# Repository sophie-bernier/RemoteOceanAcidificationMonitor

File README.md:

@file README
@author Sophie Bernier (sophie.liz.ber@gmail.com)
@brief 
@version 0.1
@date 2021-08-23

@copyright Copyright (c) 2021

@mainpage Remote Ocean Acidification Monitor Project

Grab the library from: https://github.com/sophie-bernier/RemoteOceanAcidificationMonitor

This open-source hardware and software library is designed to show how the Arduino ecosystem can be used to interface oceanographic sensors with inexpensive data logging and communications systems. The examples in this library are meant to interface the [Seabird SeapHOx](https://www.seabird.com/seaphoxv2) dissolved O<sub>2</sub> sensor and the [Pro-Oceanus CO<sub>2</sub>-Pro CV](https://pro-oceanus.com/products/pro-series/co2-pro-cv) dissolved CO<sub>2</sub> sensor with the [Adafruit Feather M0 RFM95](https://www.adafruit.com/product/3178) LoRa digital packet radio.

This project owes its existence to the support of [Dr. Brent Else](https://www.ucalgary.ca/research/scholars/else-brent), [Dr. Kristina Barclay](https://www.researchgate.net/profile/Kristina-Barclay), Dr. Richard Simms, the other researchers working at the University of Calgary, and the [Marine Environmental Observation, Prediction and Response Network's Ocean Acidification Community of Practice](https://meopar.ca/). This software package was designed to assist them as they study the exchange of greenhouse gases between the air and lakes, rivers, and oceans. Funding for this project was provided by the Natural Sciences and Engineering Research Council of Canada.

This library includes the following examples:
* LoRaInterfaceForwardingTest (LoRaInterfaceForwardingTest_Base.ino and LoRaInterfaceForwardingTest_Endpoint.ino): Attempt to use LoraPoint2PointProtocol, in an application based on LoRaRangeTest, to talk with sensors over radio. CURRENTLY UNRELIABLE due to race conditions between base and endpoint, use simpleSensorCommsEchoRadio to talk with the sensors over radio instead.
* simpleSensorCommsEchoRadio (simpleSensorCommsEchoRadio_Base.ino) and simpleSensorCommsEchoRadio_Endpoint.ino): Simplest possible implementation of radio communications interface between shore-based base and sensor-connected endpoints.
* KiCAD schematic and PCB layout (Shield_PCB_Feather) for sensor interface (TTL UART serial to/from RS-232 serial) and to power the Feather off of the same 12V external supply as the sensors.
* Serial_1_2 (Serial_1_2_RX.ino and Serial_1_2_TX.ino): How to add an additional hardware UART port on the Adafruit Feather (and other Atmel SAMD21 based Arduino-compatible boards) using the unused SERCOM (serial communication) peripherals.
* LoRaRangeTest (LoRaRangeTest_Base.ino and  LoRaRangeTest_Endpoint.ino): Uses the Adafruit Adalogger and 128x32 OLED shield to turn the sensor endpoint into a mobile range testing and evaluation unit that can change the endpoint's radio settings remotely.
* Misc. LoRa and serial examples for pycom LoPy4 boards.

All of these examples are short and simple, so additions and changes to the code should be straightforward. 

The [Tests](\Tests) folder contains additional examples of work-in-progress features such locally emulating the sensor interface.

Additional documentation, including testing and problem solving reports, can be requested from Brent Else's lab OneDrive.

*This project is published under the MIT License*

Copyright © 2021 University of Calgary

Permission is hereby granted, free of charge, to any person obtaining a copy of this software and associated documentation files (the "Software"), to deal in the Software without restriction, including without limitation the rights to use, copy, modify, merge, publish, distribute, sublicense, and/or sell copies of the Software, and to permit persons to whom the Software is furnished to do so, subject to the following conditions:

The above copyright notice and this permission notice shall be included in all copies or substantial portions of the Software.

THE SOFTWARE IS PROVIDED "AS IS", WITHOUT WARRANTY OF ANY KIND, EXPRESS OR IMPLIED, INCLUDING BUT NOT LIMITED TO THE WARRANTIES OF MERCHANTABILITY, FITNESS FOR A PARTICULAR PURPOSE AND NONINFRINGEMENT. IN NO EVENT SHALL THE AUTHORS OR COPYRIGHT HOLDERS BE LIABLE FOR ANY CLAIM, DAMAGES OR OTHER LIABILITY, WHETHER IN AN ACTION OF CONTRACT, TORT OR OTHERWISE, ARISING FROM, OUT OF OR IN CONNECTION WITH THE SOFTWARE OR THE USE OR OTHER DEALINGS IN THE SOFTWARE.

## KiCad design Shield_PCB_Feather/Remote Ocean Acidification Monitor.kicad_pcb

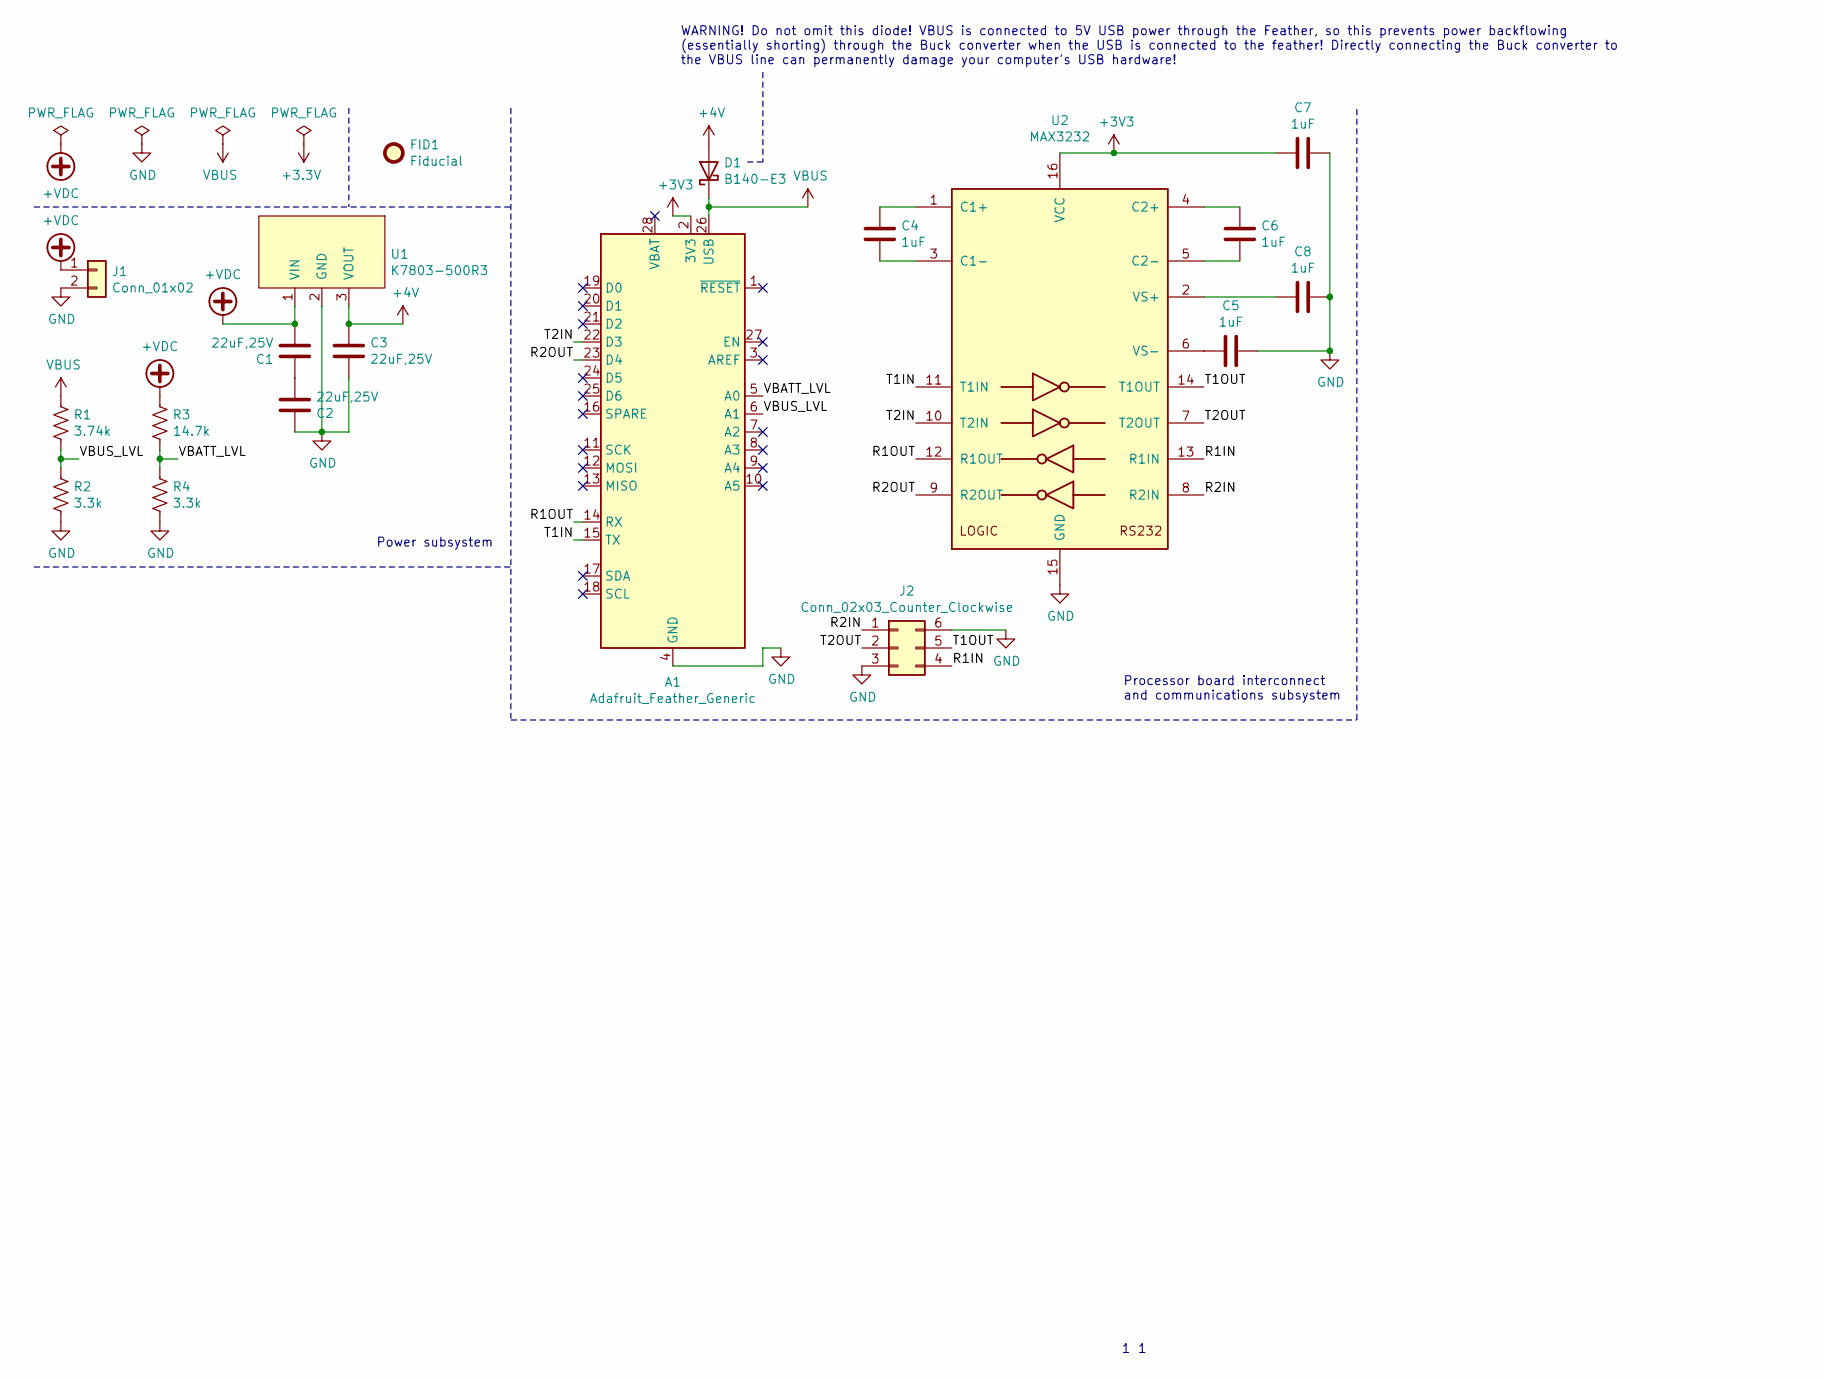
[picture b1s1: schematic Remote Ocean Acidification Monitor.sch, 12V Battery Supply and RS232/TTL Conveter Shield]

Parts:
A1: Adafruit_Feather_Generic; Adafruit_Feather_WithMountingHoles
C1, C2, C3: 22uF,25V; C_1210_3225Metric_Pad1.33x2.70mm_HandSolder
C4, C5, C6, C7, C8: 1uF; C_0805_2012Metric_Pad1.18x1.45mm_HandSolder
D1: B140-E3; D_SMA
FID1: Fiducial; Fiducial_0.5mm_Mask1.5mm
J1: Conn_01x02; Molex_Nano-Fit_105313-xx02_1x02_P2.50mm_Horizontal
J2: Conn_02x03_Counter_Clockwise; Molex_Nano-Fit_105314-xx06_2x03_P2.50mm_Horizontal
R1: 3.74k; R_0603_1608Metric_Pad0.98x0.95mm_HandSolder
R2, R4: 3.3k; R_0603_1608Metric_Pad0.98x0.95mm_HandSolder
R3: 14.7k; R_0603_1608Metric_Pad0.98x0.95mm_HandSolder
U1: K7803-500R3
U2: MAX3232; SOIC-16_3.9x9.9mm_P1.27mm

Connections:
+3V3: A1.2 (3V3), C7.2, U2.16 (VCC)
+4V: C3.1, D1.2 (A), U1.3 (VOUT)
+VDC: C1.2, J1.1, R3.1, U1.1 (VIN)
/R1IN: J2.4, U2.13 (R1IN)
/R1OUT: A1.14 (RX), U2.12 (R1OUT)
/R2IN: J2.1, U2.8 (R2IN)
/R2OUT: A1.23 (D4), U2.9 (R2OUT)
/T1IN: A1.15 (TX), U2.11 (T1IN)
/T1OUT: J2.5, U2.14 (T1OUT)
/T2IN: A1.22 (D3), U2.10 (T2IN)
/T2OUT: J2.2, U2.7 (T2OUT)
/VBATT_LVL: A1.5 (A0), R3.2, R4.1
/VBUS_LVL: A1.6 (A1), R1.2, R2.1
GND: A1.4 (GND), C2.1, C3.2, C5.1, C7.1, C8.1, J1.2, J2.3, J2.6, R2.2, R4.2, U1.2 (GND), U2.15 (GND)
unnamed: C1.1, C2.2
unnamed: C4.1, U2.1 (C1+)
unnamed: C4.2, U2.3 (C1-)
unnamed: C5.2, U2.6 (VS-)
unnamed: C6.1, U2.4 (C2+)
unnamed: C6.2, U2.5 (C2-)
unnamed: C8.2, U2.2 (VS+)
VBUS: A1.26 (USB), D1.1 (K), R1.1

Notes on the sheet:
Power subsystem
Processor board interconnect and communications subsystem
WARNING! Do not omit this diode! VBUS is connected to 5V USB power through the Feather, so this prevents power backflowing (essentially shorting) through the Buck converter when the USB is connected to the feather! Directly connecting the Buck converter to the VBUS line can permanently damage your 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

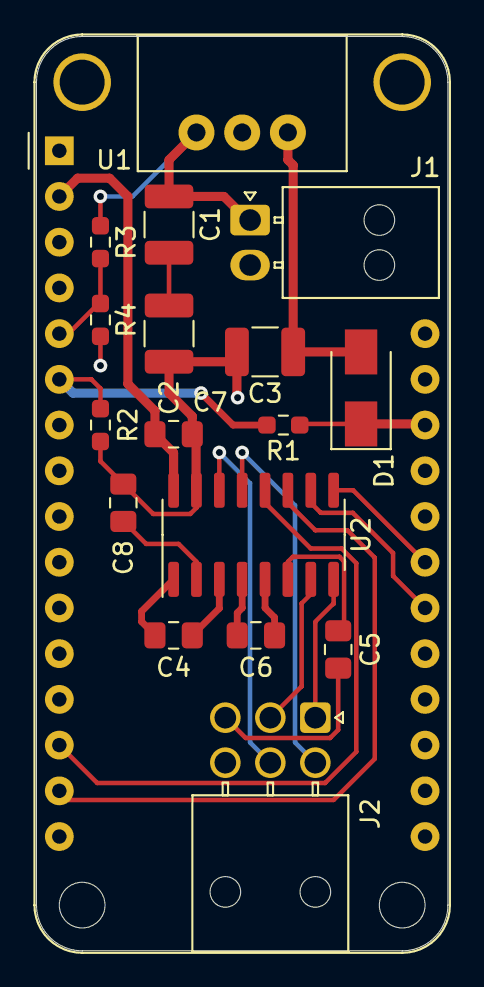
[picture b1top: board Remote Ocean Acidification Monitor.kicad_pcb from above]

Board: 2 copper layers, 22.9 x 50.8 mm, 19 parts (1 on the bottom side), 22 nets.

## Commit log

2021-05-04 Added ufl connector and processor datasheet
2021-05-14 Added Examples folder with radio TX/RX demo (Feather9x_RX and Feather9x_TX), UART on additional serial ports demo (Serial_1_2_RX and Serial_1_2_TX), and echo serial over radio demo (serialEcho). Also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
2021-06-09 Set up echo scripts for LoRa and Serial Added proO templates Added pinouts
2021-06-10 Added sketches for lora range tests - endpoint sends out 'hello world' at fixed SF, BW, TX power, freq. every 5s.
2021-06-14 Added pycomBlink example for blinking pycom boards. pycomBlink2 is an empty project with just a pymakr.conf file so that I can access the REPL for both devices simultaneously by opening a separate wi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
2021-06-16 Added pycom examples. Added LoRaRangeTest (for future development) and downgraded LoRaRangeTest_v1 examples (with a simpler structure to test the basic functionality of radiohead's RealiableDatagram 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
2021-06-16 Moved docs to new folder called 'docs'. Added template files for loraPoint2PointProtocol, which will contain the common functions for LoRaRangeTest and the rest of the stuff for full point-to-point n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
2021-06-16 Moved common functions between LoRaRangeTest sketches into loraPoint2PointProtocol library. setupRadio forceRadioReset setFrequencyChannel setSpreadingFactor setBandwidth buildStringfromSerial servic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
2021-06-16 Modified LoRaRangeTest_Base and LoRaRangeTest_Endpoint to use loraPoint2PointProtocol library.
2021-06-17 Added broken callback function and set tx power function. Going to commit this and then remove the stuff that doesn't work and replace it with proper individual callbacks. Lesson: Don't mix C-strings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
2021-06-17 Removed broken callback function. I plan on replacing it with a minimum of other callbacks.
2021-06-17 Removed references to broken callback from example functions.
2021-06-17 Added message structs ro replace existing simple variables.
2021-06-18 Added RX and TX ind callback things. Serial statements are kept in for debugging.
2021-06-18 Added support for tx ind and rx ind callback processing to LoRaRangeTest examples, including basic SD card logging for LoRaRangeTest_Base.
2021-06-18 Changed setupRadio to return true if successful and false if unsuccessful, instead of returning nothing. This allows the application to know whether or not starting the radio was successful.
2021-06-18 Added basic functionality to show received and transmitted messages with their timestamps, addresses, and acknowlegement statuses on the 128x32 LCD
2021-06-18 Set TX power using loraPoint2Point::setTxPower instead of rfm95 equivalent to test use of this function. Set frequency in loraPoint2Point::setupRadio so frequency is explicitly defined and to test lo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
2021-06-22 Added functions for ober the air link changing. In loraPoint2Point::setupRadio(), changed setSpreadingFactor, setBandwidth, and setFrequencyChannel to use defaults defined in preprocessor statements 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
2021-06-22 Test to use credential.
2021-06-22 Removed the simple change I made to test logon with a token credential.
2021-06-23 Added postscript ++ operator to spreadingFactor_t, signalBandwidth_t, and frequencyChannel_5 to help cycle through options. Added debug command mode to buildStringFromSerialInner, so that "!" charact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
2021-06-23 Defined names for buttons A, B, and C (BUTTON_SETTING_SELECT, BUTTON_VALUE_SELECT, and BUTTON_ENTER respectively) for readability. Current radio settings are logged to SD card. Changed endpoint code 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
2021-06-25 RF95 needs to be set to mode idle after setting the spreading factor, bandwidth, frequency, and TX power, as some of these settings require the radio set to mode idle for the changes to take effect. 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
2021-06-28 Added loraPoint2Point::updatePacketErrorFraction, loraPoint2Point::resetPacketErrorFraction, and loraPoint2Point::getPacketErrorFraction to maintain a running average of the packet error rate. Added 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
2021-06-28 Added linkChangeInd definition to loraRangeTest base application, which just updates the local variables that track the radio settings. Added function prototypes into which some of the main code will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
2021-07-02 Changed radio setting setter functions to return instead of setting the radio to default values. This prevents bad values from putting a radio into a non-communicating state.
2021-07-02 Deprecated 625kHz bandwidth setting, because the RFM95 does not actually accept that as an argument. Defined minimum TX power as 2 instead of 1, because the RFM95 driver does not accept values below 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
2021-07-02 Wrap around tx power to MIN_txPower instead of 1 to maintain goal of minimizing magic numbers. Added linkChangeInd definition to endpoint to prevent code from entering a random pointer and screwing u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
2021-07-02 Documentation update. Added file descriptions to simpleTimer.h, loraPoint2PointProtocol.cpp, and loraPoint2PointProtocol.h. Added descriptions to structs, enums, classes, and all public member functi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
2021-07-05 Fixed problem in loraPoint2PointProtocol where the user could not set frequency channels above 9 in command mode.
2021-07-05 Put fields of sd logs for rx and tx indications in the right order.
2021-07-07 Added work-in-progress proO files to support pro oceanus sensor. Currently only the data parsing is working.
2021-07-07 Modified simpleSensorCommsEcho sketch to automatically tell the sensor to return its sampled data every 10s once started, and to stop returning the sampled data 20s after reading it starts. This is s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
2021-07-07 Refactored messy code as FSM using nested switch statements.
2021-07-08 Continued refactoring proO to use FSM.
2021-07-08 Added compile guards to loraPoint2PointProtocol and simpleTimer
2021-07-08 Added case to start viewing logged data from a sleep state.
2021-07-12 Changed packet error fraction code to track number of unsuccessful and total packets, allowing us to trigger a setting reset if a certain number of packets fail.
2021-07-13 Changed averaging to use an exponential moving average of period 6.
2021-07-13 Tied RFM95_CS high on start to limit the likelihood of that line being caught low on startup, causing a conflict between the SD and RFM95 SPI pins.
2021-07-13 test commit
2021-07-14 added heartbeat message to maintain link base sends this out to all endpoints repeatedly after a link change, if it does not recieve a response, it reverts its radio settings
    After recieving a linkChangeRsp, instead of stopping linkChangeTimeoutTimer, serviceLinkChangeRsp resets it and extends the timeout using the new setTimeout function.
    linkChangeTimeoutTimer still calls linkChangeReqTimeout to revert settings when it times out.
    successfully recieving a message resets linkChangeReqTimeout, and if SUCCESSFUL_PACKETS_BEFORE_LINK_IS_TRUSTED packets or acknowlegements are recieved, it trusts the link and stops the timer.
2021-07-14 undo test commit
2021-07-14 Start heartbeats on base.
2021-07-15 Simple sensor comms testing upgrade Added $ to input char ignore list so it isn't output along with the ESC character. Set default transmission power to two from 15. Re enabled reading from serial po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
2021-07-16 Added the interface forwarding test examples using rhReliableDatagram and including simple toggles to simplify debugging the timing. Added similar toggles to the simple echo example.
2021-07-16 Added in an additional toggle on pin 17 that goes high when send to wait is active. These changes are tagged as ‘ps7-2’.
2021-07-16 decreasing sendToWait timeout to 100 ms.
2021-07-16 To get a detailed average of the time takes to transmit with different send to wait time outs, I’ll remove the toggles before the timing interval and export the data to CSV files.
2021-07-19 simpleSensorCommsEchoRadio_Base recognizes & as '\r' to input cmds for seaphox.
2021-07-19 Added faster/cleaner input handler tested in simpleSensorCommsEchoRadio_Endpoint to simpleSensorCommsEchoRadio_Base. Increased message length to 255 to work with seaphox. Changed baud rate to 4800 to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
2021-07-21 Upgraded the endpoint simple sensor echo script to be able to select between sending a message to the Seaphox and sending a message to the pro CV. The pro CV is selected by adding a % to the start of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
2021-07-21 Added loraPoint2PointProtocolLightweight.h which only contains the message ids.
2021-07-21 Added sensors.h to hold a list of sensors.
2021-07-23 Added checksums for data recieved and sent via radio. Added experimental DSSS features using the upgraded RF95 library at https://github.com/Sebastien-B/RadioHead_RFM95LoRaFHSS The base by default st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
2021-07-26 Added & -> '\r' conversion for buildStringFromSerial
2021-07-26 Disabled frequency hopping and set frequency to 903.0 by default.
2021-07-27 Set Serial1 to run at 4800baud for seapHOx, commented out waitCAD because rf95 is not public
2021-07-28 Fixed serviceTx to actually call user.txInd(buf, bufLen, destAddress, acknowleged); with acknowleged = true, when an acknowlegement is recieved. Previously it was always calling it with acknowleged =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
2021-07-28 Added DEBUG_MAKE_RELIABLE_DATAGRAM_PUBLIC and DEBUG_MAKE_RF95_PUBLIC, required for lora interface forwarding tests. Replaced "if" statement tree in buildStringFromSerialInner with a switch statement 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
2021-07-28 Started serial1 on 4800 baud on loraInterfaceForwardingTest so that it works with the seapHOx. Added 50ms delays after transmission on loraInterfaceForwardingTest_Endpoint to avoid race conditions. \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
2021-07-28 Added acknowledgement message id
2021-07-28 Added simple acknowledgement feature enabled with the ENABLE_ACK switch. Added println() at start of rx in case rx interrupts incoming characters.
2021-08-09 Added support for serial2 port (tx on pin 10, rx on pin 11) to simpleSensorCommsEcho to allow testing both serial ports. Set to 4800 baud as this is the baud rate used by the seaphox in simpleSensorC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
2021-08-09 Added documentation to LINK_CHANGE_TIMEOUT_MILLIS to test if doxygen recognizes it.
2021-08-09 Added file header to simpleSensorCommsEchoRadio_Endpoint to test if doxygen documents .ino files.
2021-08-12 Add doxygen comments to examples.
2021-08-12 Added documentation to unfinished proO and msgTypes
2021-08-18 Fixed loraPoint2Point::serviceTx so that messages to broadcast address 0xFF are not counted as unacknowledged by the packet error fraction update. Heartbeat response is sent only to the source addres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
2021-08-23 deleted unused simpleTimer.cpp
2021-08-23 Major documentation happened here.
2021-08-24 Added kicad files under Shield_PCB_Feather.
2021-08-24 Fixed missing/incorrect license, name, and email
2021-08-24 Made all doxyfile paths relative
2021-08-24 Updated all documentation
2021-08-24 Added ENABLE_USB_SERIAL to LoRaRangeTest_Base and simpleSensorCommsEchoRadio_Endpoint to allow them to be mobile w/o needing to comment out the serial init. Added identifiers messages on serial to Lo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
2021-08-26 Moved deprecated examples to DEPRECATED folder
2021-08-27 Attempt to implement "ping pong" buffer system. Currently has two message buffers for data received from each sensor. When the first message buffer is full, containing a message that is ready to be t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
2021-08-27 Enabled digital pins 14 through 18 for logic analyzer debugging. Pin 14: Goes high for duration of uart recieve operation. Pin 15: Goes high for duration of radio transmit operation. Operates as expe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
2021-09-13 2. Against PS13H2, rewrite the code to use two separate arrays with a pointer used to point to the active and done array. If letters are still cut off… H2 is refuted. These changes are tagged as ps13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
2021-09-14 Bumped USB serial baud rate on simpleSensorCommsEchoRadio_Endpoint up to 500k baud from 115.2k baud to lessen the likelihood that the USB serial contributes to timing faults. Commented out and shorte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
2021-09-14 Streamlined flow control by only declaring a buffer to be "done" if its payload length is nonzero instead of throwing out nonzero payload length done messages.
